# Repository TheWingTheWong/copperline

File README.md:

# copperline

A PCB autorouter written from scratch in Rust: it reads a KiCad 9 board, routes every
connection on a grid with negotiated congestion (PathFinder), checks the result against
exact copper geometry, and writes plain KiCad tracks and vias back into the file. It also
compiles to a 440 KB WebAssembly module, so the [browser demo](https://thewingthewong.github.io/copperline/web/)
routes boards on your machine with no server.

<!-- headline:start -->
On 86 real open-hardware boards of medium size, set aside before development began and routed one at a time with the same input files and scored by KiCad 9's own DRC, copperline produces **94% clean boards against Freerouting's 66%** (71% if Freerouting is forgiven the errors KiCad's DSN export causes), with a median of 2.2 s per board against 20 s. On 90 hard boards it routes 80% clean (median 11 s) with a deterministic effort budget.
<!-- headline:end -->

## Try it

```sh
cargo install --git https://github.com/TheWingTheWong/copperline
copperline route board.kicad_pcb -o board-routed.kicad_pcb
```

The design rules are read from `board.kicad_pro` next to the board (net classes, track
widths, clearances, via sizes, board minimums). Without it, KiCad's defaults apply. The
output is the input file byte for byte, with the new `segment` and `via` items appended
before the final parenthesis, so it opens in KiCad 9 and diffs cleanly.

A board that ships with the repo:

```sh
cargo run --release -- route examples/mcu48.kicad_pcb -o /tmp/mcu48-routed.kicad_pcb --stats /tmp/stats.json
```

```
pitch 0.087 mm, 42 nets, 62/62 connections, 18 iterations, 544 tracks, 54 vias, 1267.9 mm, 7985 ms, effort 8M
```

`scripts/check_examples.sh` routes both bundled boards and scores them with `kicad-cli`
(both come back with zero violations and zero unconnected items).

The browser demo in `web/` is static; rebuild its module with
`cargo build --release --lib --target wasm32-unknown-unknown && cp target/wasm32-unknown-unknown/release/copperline.wasm web/`
(CI builds the same target on every push).

Other commands: `copperline info` (what the parser saw), `copperline svg` and
`copperline render` (pictures of a board), `--frames DIR` on `route` (one image per
routing step; `scripts/animate.sh` turns them into the GIF above).

## Results

<!-- results:start -->
#### Head to head, one board at a time (current build)

| tier | boards | copperline clean | Freerouting clean | Freerouting, conversion artifacts forgiven | copperline median / p90 s | Freerouting median / p90 s | both clean | only copperline | only Freerouting |
|---|---:|---:|---:|---:|---:|---:|---:|---:|---:|
| medium, held out | 86 | 81/86 = 0.94 [0.87, 0.97] | 57/86 = 0.66 [0.56, 0.75] | 61/86 = 0.71 [0.61, 0.79] | 2.2 / 11.6 | 20.1 / 224.7 | 55 | 26 | 2 |

| copperline alone | boards | clean | median / p90 / max s |
|---|---:|---:|---:|
| hard, held out | 90 | 72/90 = 0.80 [0.71, 0.87] | 10.9 / 144.1 / 280 |

copperline build for these rows: bench-freeze-36-g6f14213, bench-freeze-40-ge998a5f, default effort budget. Run twice, the hard-tier result was identical (clean, unconnected, track and via counts) on 90 of 90 boards.

#### Earlier run: frozen build, both routers sharing a loaded laptop

| tier | boards | copperline clean | Freerouting clean | Freerouting, conversion artifacts forgiven | copperline median / p90 s | Freerouting median / p90 s | both clean | only copperline | only Freerouting |
|---|---:|---:|---:|---:|---:|---:|---:|---:|---:|
| easy (seen in dev) | 96 | 96/96 = 1.00 [0.96, 1.00] | 81/96 = 0.84 [0.76, 0.90] | 85/96 = 0.89 [0.81, 0.93] | 0.4 / 2.2 | 22.1 / 63.6 | 81 | 15 | 0 |
| medium, held out | 86 | 79/86 = 0.92 [0.84, 0.96] | 56/86 = 0.65 [0.55, 0.74] | see head-to-head | 3.0 / 18.8 | 33.5 / 541.3 | 54 | 25 | 2 |
| hard, held out | 90 | 52/90 = 0.58 [0.47, 0.67] | 36/90 = 0.40 [0.30, 0.50] | 36/90 = 0.40 [0.30, 0.50] | 83.6 / 414.9 | 600 (cap) / 600 (cap) | 31 | 21 | 5 |

#### copperline on every board of each tier (not only those Freerouting finished)

| tier | boards routed | clean | boards where KiCad found errors in copperline's copper |
|---|---:|---:|---:|
| easy (seen in dev) | 96 | 96/96 = 1.00 [0.96, 1.00] | 0 |
| medium, held out | 86 | 79/86 = 0.92 [0.84, 0.96] | 1 |
| hard, held out | 90 | 52/90 = 0.58 [0.47, 0.67] | 1 |

copperline's own DRC vs KiCad: KiCad found errors in copperline's copper on 2 of 952 routed board runs (0282_WordClock_v2.0_WordClock_v2, 0595_LoRaPP_loramod).

#### Parity with PCBWorld's published Freerouting run (D3-A)

PCBWorld (RQ2 table, d3a fair-95 subset, Freerouting 2.1.0, mean of 4 seeds) reports mean DRC violations 0.09 on fully routed boards and routability 0.98 (mean fraction of nets routed). Clean-pass is not published, so this compares what can be compared:

- our single-seed run on test-a: routability 0.97 (PCBWorld: 0.98), mean DRC violations on fully routed boards 0.15 (PCBWorld: 0.09; ours includes the DSN-conversion artifacts above), 85/96 boards fully routed
- clean-pass of our run: 81/96

The slowest completed held-out copperline run took 1774 s; the frozen build ran into the bench's 1800 s cap on 0672_DAC-ADAU1966_DAC-ADAU1966, because its time budget was only checked between negotiation passes (the current build stops on a deterministic effort budget instead; see Limitations).
<!-- results:end -->

**Setup.** Every board in these tables is a real open-hardware design from
[PCBench](https://github.com/PCBench/PCBench), prepared with
[PCBWorld](https://github.com/LGAI-Research/PCBWorld)'s own pipeline (the D3 benchmark):
the original routing is stripped, each net keeps the width its designer used, and the
project's design rules come along in the `.kicad_pro`. Both routers get the same files. A
board is **clean** when KiCad 9's DRC (`kicad-cli pcb drc`, error severity) reports zero
unconnected items and zero violations: PCBWorld's clean-pass. Freerouting 2.1.0 runs as
PCBWorld runs it (`-mp 10`, headless, default seed) through KiCad's DSN export and SES
import, with a 600 s cap per board. Rates carry Wilson 95% intervals; "both / only" count
the boards each router got clean.

**The two runs.** The head-to-head table is the one to trust. It uses the current build,
whose stopping point is a deterministic effort budget (A* expansions), so its result for a
board does not depend on machine load. Freerouting ran one board at a time on an otherwise
quiet laptop, alongside the copperline run as the only other process. Freerouting was not
rerun on the hard tier, because at up to 10 minutes a board that takes most of a day. The
earlier run below used the frozen build, whose budget was wall-clock time, with both
routers and several of their copies sharing a loaded laptop. The load slowed both by large
factors (board 0602 took the frozen copperline 313 s in that run and 7.6 s on a quieter
machine). Its times and its hard-tier rates are therefore indicative only, and they are
kept because that run was the held-out one: it was made once, before any of the fixes
below.

**Why Freerouting loses boards.** On medium boards it mostly stops with a connection or
two unrouted after PCBWorld's `-mp 10` passes; on hard boards it mostly runs out of time.
Its DRC errors are mostly not routing mistakes: KiCad's DSN export carries no copper text
and no footprint-level clearance overrides, and the SES that comes back has widths rounded
to the DSN resolution. `bench/classify.py` labels every KiCad error by cause, and the
"conversion artifacts forgiven" column counts a fully connected Freerouting board as clean
when all its errors are of those kinds. The plain column is what a user of the
KiCad-Freerouting round trip gets. copperline reads the `.kicad_pcb` directly and sees the
text and the overrides: an advantage of the approach, not cleverer routing.

**Where copperline fails.** It leaves connections out. It checks its copper with its own
exact DRC before writing and drops whatever fails. KiCad found errors in copperline's
copper on two boards of the frozen run, both bugs in that DRC, since fixed with tests: a
plated through-hole pad listing only F.Cu (KiCad treats it as copper on every layer), and
two tracks 0.1493 mm apart that fell into different buckets of the DRC's spatial index.

**Provenance.** Rows written since the `commit` column was added name the copperline build
that produced them. The frozen run predates it; `target/release` was built only from
commits whose `src/` matches `bench-freeze` until that run ended (`git diff bench-freeze
1de4fa8 -- src` is empty). Board 0498 is dropped for both routers: KiCad 9's
`ImportSpecctraSES` rejects Freerouting's session file for it. Per-board results are in
[`bench/results/per-board.md`](bench/results/per-board.md).

Three held-out boards from the head-to-head run, side by side (left copperline, right
Freerouting, same input file; solid blocks are copper text, drawn as the boxes copperline
keeps clear of).

**Freerouting is not deterministic.** Between its two runs on the same 86 medium boards,
19 boards flipped between clean and not clean (10 one way, 9 the other), while the total
moved by one (56 and 57). The totals are stable; the per-board "only" counts are one sample.

**How held out is "held out".** The sealed boards were set aside before any router code
existed and the frozen run routed them once. Two of copperline's later fixes came from
KiCad findings on sealed boards (the PTH pad on 0282, the DRC bucket on 0595), and the
default effort budget was set after the hard-tier runs, so the head-to-head numbers are on
boards the current build has been exposed to; the frozen run is the strictly held-out one.
The reproducibility check compares the deterministic hard-tier run with an earlier one whose
rows name a `-dirty` checkout; the routing code is identical in both (only `--version` and
`render`'s file-name check differ).

Every number in this section is written by `python3 bench/report.py` from the per-board
CSVs in `bench/results/` (and into `bench/results/summary.md`). Times are each router's
own wall time per board on an 8 GB Apple M-series laptop; for Freerouting this includes JVM
start (about 1 s). DSN export, SES import and KiCad's DRC are not counted. The frozen run
started with PCBWorld's 1800 s cap for Freerouting and moved to 600 s part way through the
hard tier, once Freerouting had returned no clean board after 600 s in 15 runs; copperline
kept 1800 s there and went past 600 s on 4 hard boards, none of them clean, so the
uneven cap changes no result. PCBWorld also reports a best-of-4-seeds Freerouting number,
which neither run attempts.

### A note on the benchmark's splits

PCBWorld ships D3 as train and test splits, but every test board is also a train board:
the easy test split is the easy train split (99 of 99), and all 10 medium and all 10 hard
test boards appear in the corresponding train lists too (check: `bench/d3_pcbworld.json`).
Anyone tuning on train and reporting on test is reporting on boards they have seen.
copperline was developed on the train pools, so before writing any router code
`bench/splits.py` sealed 86 medium and 92 hard train boards (seed 20261110). Those sealed
boards are the **held-out** tiers above; the test boards add nothing held out, since they
all sit in the development pools or in the sealed sets. The easy tier was seen during
development and is labelled that way.

5 of the 796 D3 board folders could not be rebuilt by the prep chain on this machine
(0001, 0002, 0030, 0564, 0647) and are left out for both routers.

## How it works

**Parsing.** A small S-expression reader loads the `.kicad_pcb`: copper layers, nets,
footprints with pads (circle, rect, roundrect, oval, trapezoid, chamfered and custom pads,
each turned into exact shapes: points, capsules and polygons with a rounding radius), drill
holes, the board outline from Edge.Cuts (lines, arcs, circles, polygons, including those
inside footprints), rule-area keepouts, existing copper and copper text. Text is boxed
with the real advance widths of KiCad's stroke font, measured from pcbnew.

**Rules.** Net classes and patterns, track widths, clearances, via sizes, copper-to-edge,
hole clearance and hole-to-hole come from the `.kicad_pro`, along with pad- and
footprint-level clearance overrides.

**Grid and masks.** Each copper layer becomes a grid (pitch from the narrowest
width + clearance, typically 0.06 to 0.1 mm). For every net class, a mask records per cell
whether a track centreline of that class may sit there: free, owned by one net (inside
that net's clearance halo, so only that net may pass), or blocked. The mask is built from
exact distances to the real shapes, inflated by half the track width, the larger of the two
clearances, and a margin of 0.71 of a grid step, which is the furthest a straight or
diagonal grid move strays from a cell centre. A second mask per class does the same for via
centres, across all layers and with hole rules.

**Pads.** A pad is reached through its rim cells, or through a short exact stub from the
pad centre to a nearby grid node. Fine-pitch pads (0.5 mm QFP, QFN, FPC and USB-C rows)
leave straight along their axis before bending onto the grid, because an angled stub
clips the neighbouring pads. Every stub is checked against the exact geometry before it
is offered to the search.

**Routing.** Each net is grown as an approximate Steiner tree: a multi-source A* runs from
everything already connected to the nearest unconnected pad, with 8-way moves, through
vias between layers, a mild per-layer direction preference and a bend cost. The search
stays inside a window around the connection first, with a heuristic weight of 1.25.

**Negotiation.** In the first pass, nets may overlap. Every routed net stamps a halo into
an occupancy grid per net class. After each pass, a cell used by more than one net raises
its history cost, the present-congestion factor grows (capped), and only the nets in
conflict are ripped up and rerouted. This repeats until nothing overlaps (McMurchie and
Ebeling's PathFinder, 1995). If it stalls, the remaining nets are rerouted with other nets'
halos as hard walls.

**Exact check.** The result is checked segment by segment against pads, holes,
existing copper, the board edge, keepouts and the other new copper, using the exact
distance functions. A net that still violates is rerouted strictly or, failing that, left
unrouted. When a board ends up incomplete, the
whole route is retried on a finer grid (0.6x, then 0.4x pitch) within one time budget.

**Writing.** Grid paths become straight runs (collinear moves merged, breakpoints kept
where another branch joins), then KiCad `segment` and through `via` items with fresh UUIDs.

## Testing

`cargo test` covers the distance kernel against dense sampling (randomised), the
S-expression reader, rules and wildcard net-class patterns, the writer, and the router on
generated boards. Random two-layer boards and a 0.5 mm-pitch QFN-24 fan-out must come back
with zero violations under copperline's DRC. Every net the router reports as complete must
also be connected according to an independent connectivity check that follows KiCad's rules,
and the output must strip back to the input byte for byte.

On real boards, every result in `bench/results/` was scored by `kicad-cli`. Disagreements
between copperline's DRC and KiCad's are counted in the results above. The pad parser is also checked directly against KiCad: `bench/check_parser.py`
has pcbnew dump every pad's own copper polygon and requires each vertex to lie inside
copperline's shape (`bench/results/parser-*.txt`). Over the development pools and both
sealed sets (473 boards, 45,197 pads), no KiCad pad copper lies outside copperline's shapes.

## Reproducing the benchmark

```sh
git clone https://github.com/PCBench/PCBench            # ~1.2 GB of open-hardware boards
git clone https://github.com/LGAI-Research/PCBWorld pcbworld   # its BSD-3 prep chain
PCBENCH=PCBench PCBWORLD=pcbworld D3_ROOT=$PWD/d3 bench/prepare.sh
D3_ROOT=$PWD/d3 python3 bench/run.py --split sealed-b --router copperline
D3_ROOT=$PWD/d3 FREEROUTING_JAR=freerouting-2.1.0.jar python3 bench/run.py --split sealed-b --router freerouting
python3 bench/report.py
```

`bench/run.py` needs KiCad 9 (`KICAD_CLI`, and `KICAD_PYTHON` for a Python that imports
`pcbnew`), Java for Freerouting (`JAVA`), and runs one board at a time so it fits on a
small laptop. It resumes where it stopped. Board files are never committed here; the
splits are in `bench/splits.json`.

## Limitations

- Grid routing: tracks run at 0/45/90 degrees between grid nodes. There is no any-angle
  routing, no push-and-shove, and no pull-tight pass yet, so routes have more bends than a
  person would draw.
- Through vias only (no blind or buried vias). No differential pairs, length matching or
  impedance control. Copper pours are treated as fixed obstacles and are not created.
- On fine-pitch parts in tight spots (USB-C receptacles, FPC connectors) the grid sometimes
  cannot find a legal entry and leaves a connection unrouted. That is where most of the
  held-out failures above come from.
- copperline reads a `.kicad_pcb` the way KiCad 9 writes it. Older files should be opened
  and saved once in KiCad 9 first.
- Hard boards can take minutes, because A* floods behind large blocked areas. `--effort`
  (in millions of A* expansions, 150 by default, about two minutes on this laptop for the
  hardest boards) decides where routing stops, so the same input always gives the same
  output. `--budget` (600 s) is only a wall-clock safety net (the first, coarse attempt gets
  60% of it); the slowest hard board here needed 280 s, so on a machine more than about
  1.3x slower, or in the browser (which uses a 60 s budget), that net can cut a route short
  and results can again depend on time. A board that runs out of effort is written legal but
  incomplete, and `copperline` exits with code 2.
- The browser demo runs the same code in WebAssembly, somewhat slower than native; dense
  boards take a while there.

## References

- L. McMurchie and C. Ebeling, "PathFinder: A Negotiation-Based Performance-Driven Router
  for FPGAs", FPGA 1995.
- Song et al., "PCBWorld: A Benchmark Environment for Engine-Grounded PCB Design Automation",
  KDD 2026 workshop, [arXiv:2607.05915](https://arxiv.org/abs/2607.05915),
  [code](https://github.com/LGAI-Research/PCBWorld): the D3 benchmark and its prep chain
  (BSD-3), used here unchanged.
- [PCBench](https://github.com/PCBench/PCBench): the open-hardware board collection.
- [Freerouting](https://github.com/freerouting/freerouting): the baseline router.
- KiCad 9 file format and `kicad-cli` DRC: the ground truth for every number here.

## How this was made

copperline was written by an AI coding agent (Anthropic's Claude), working unattended over
several sessions, as one of a series of daily build projects; the commits say so. The
parser and geometry kernel come from an earlier attempt at the same project, as the first
commit notes. Every number above comes from scripts in this repo, and the held-out boards
were sealed before any router code existed.

## License

MIT, see [LICENSE](LICENSE).

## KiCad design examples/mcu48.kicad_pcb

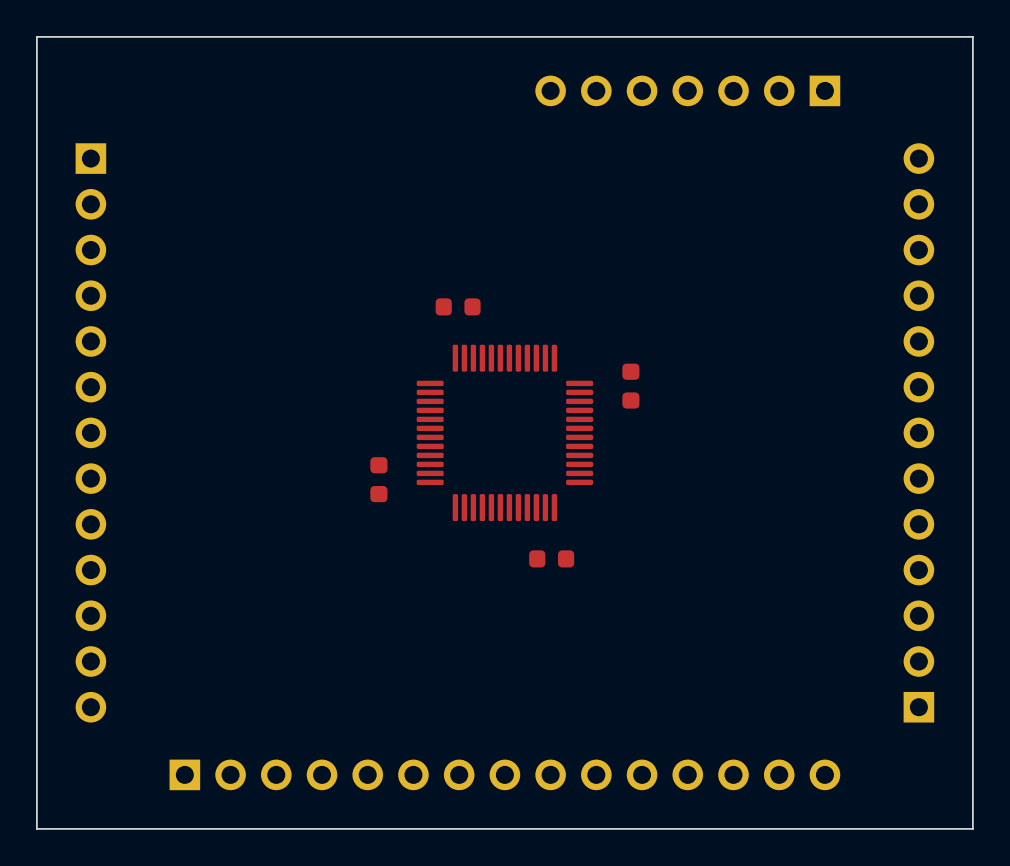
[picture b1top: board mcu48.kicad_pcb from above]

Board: 2 copper layers, 52.0 x 44.0 mm, 9 parts (0 on the bottom side), 42 nets, no tracks yet.

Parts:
C1: C1
C2: C2
C3: C3
C4: C4
J1: J1
J2: J2
J3: J3
J4: J4
U1: U1

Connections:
+3V3: C1.1, C2.1, C3.1, C4.1, J1.2, J2.2, J3.2, J4.2, U1.12, U1.24, U1.36, U1.48
GND: C1.2, C2.2, C3.2, C4.2, J1.1, J2.1, J3.1, J4.1, U1.11, U1.23, U1.35, U1.47
P1: J3.12, U1.1
P2: J3.13, U1.2
P3: J4.3, U1.3
P4: J4.4, U1.4
P5: J4.5, U1.5
P6: J2.4, U1.6
P7: J4.7, U1.7
P8: J1.3, U1.8
P9: J1.4, U1.9
P10: J1.5, U1.10
P13: J1.6, U1.13
P14: J1.7, U1.14
P15: J1.8, U1.15
P16: J1.9, U1.16
P17: J1.10, U1.17
P18: J1.11, U1.18
P19: J1.12, U1.19
P20: J1.13, U1.20
P21: J2.3, U1.21
P22: J4.6, U1.22
P25: J2.5, U1.25
P26: J2.6, U1.26
P27: J2.7, U1.27
P28: J2.8, U1.28
P29: J2.9, U1.29
P30: J2.10, U1.30
P31: J2.11, U1.31
P32: J2.12, U1.32
P33: J2.13, U1.33
P34: J2.14, U1.34
P37: J2.15, U1.37
P38: J3.3, U1.38
P39: J3.4, U1.39
P40: J3.5, U1.40
P41: J3.6, U1.41
P42: J3.7, U1.42
P43: J3.8, U1.43
P44: J3.9, U1.44
P45: J3.10, U1.45
P46: J3.11, U1.46

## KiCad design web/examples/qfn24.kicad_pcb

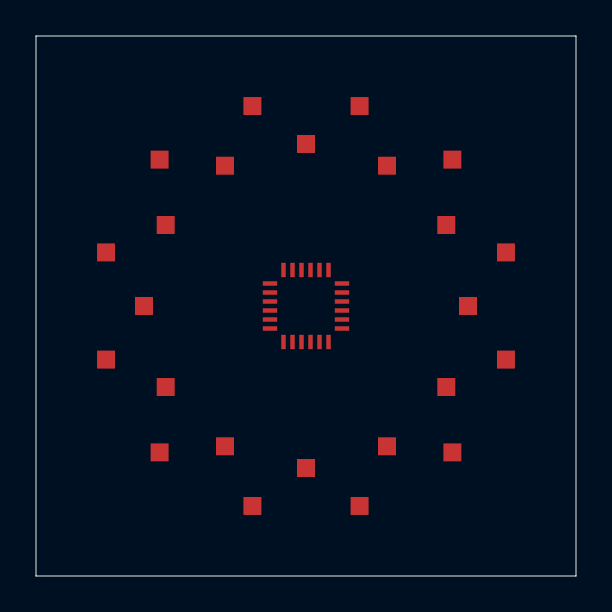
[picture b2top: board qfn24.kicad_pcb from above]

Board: 2 copper layers, 30.0 x 30.0 mm, 48 parts (0 on the bottom side), 24 nets, no tracks yet.

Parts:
U0, U1, U2, U3, U4, U5, U6, U7, U8, U9, U10, U11, U12, U13, U14, U15, U16, U17, U18, U19, U20, U21, U22, U23, U24, U25, U26, U27, U28, U29, U30, U31, U32, U33, U34, U35, U36, U37, U38, U39, U40, U41, U42, U43, U44, U45, U46, U47: P

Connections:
N1: U0.1, U1.1
N2: U2.1, U3.1
N3: U4.1, U5.1
N4: U6.1, U7.1
N5: U8.1, U9.1
N6: U10.1, U11.1
N7: U12.1, U13.1
N8: U14.1, U15.1
N9: U16.1, U17.1
N10: U18.1, U19.1
N11: U20.1, U21.1
N12: U22.1, U23.1
N13: U24.1, U25.1
N14: U26.1, U27.1
N15: U28.1, U29.1
N16: U30.1, U31.1
N17: U32.1, U33.1
N18: U34.1, U35.1
N19: U36.1, U37.1
N20: U38.1, U39.1
N21: U40.1, U41.1
N22: U42.1, U43.1
N23: U44.1, U45.1
N24: U46.1, U47.1

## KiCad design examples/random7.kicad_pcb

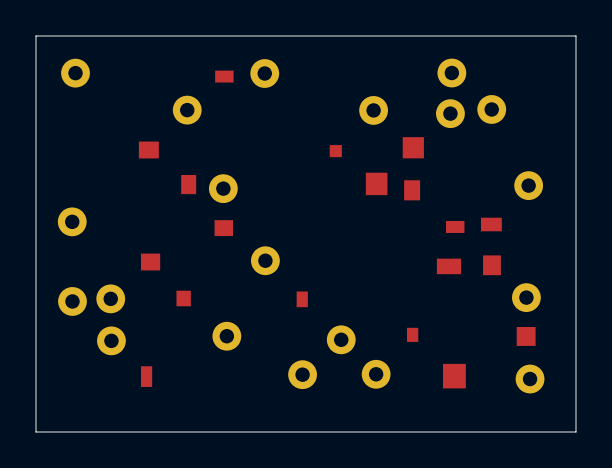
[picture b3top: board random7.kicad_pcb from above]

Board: 2 copper layers, 30.0 x 22.0 mm, 39 parts (0 on the bottom side), 11 nets, no tracks yet.

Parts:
U0, U1, U2, U3, U4, U5, U6, U7, U8, U9, U10, U11, U12, U13, U14, U15, U16, U17, U18, U19, U20, U21, U22, U23, U24, U25, U26, U27, U28, U29, U30, U31, U32, U33, U34, U35, U36, U37, U38: P

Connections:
N1: U0.1, U1.1, U2.1, U3.1
N2: U4.1, U5.1, U6.1, U7.1
N3: U8.1, U9.1, U10.1, U11.1
N4: U12.1, U13.1, U14.1, U15.1
N5: U16.1, U17.1, U18.1, U19.1
N6: U20.1, U21.1, U22.1
N7: U23.1, U24.1, U25.1, U26.1
N8: U27.1, U28.1
N9: U29.1, U30.1, U31.1, U32.1
N10: U33.1, U34.1
N11: U35.1, U36.1, U37.1, U38.1
